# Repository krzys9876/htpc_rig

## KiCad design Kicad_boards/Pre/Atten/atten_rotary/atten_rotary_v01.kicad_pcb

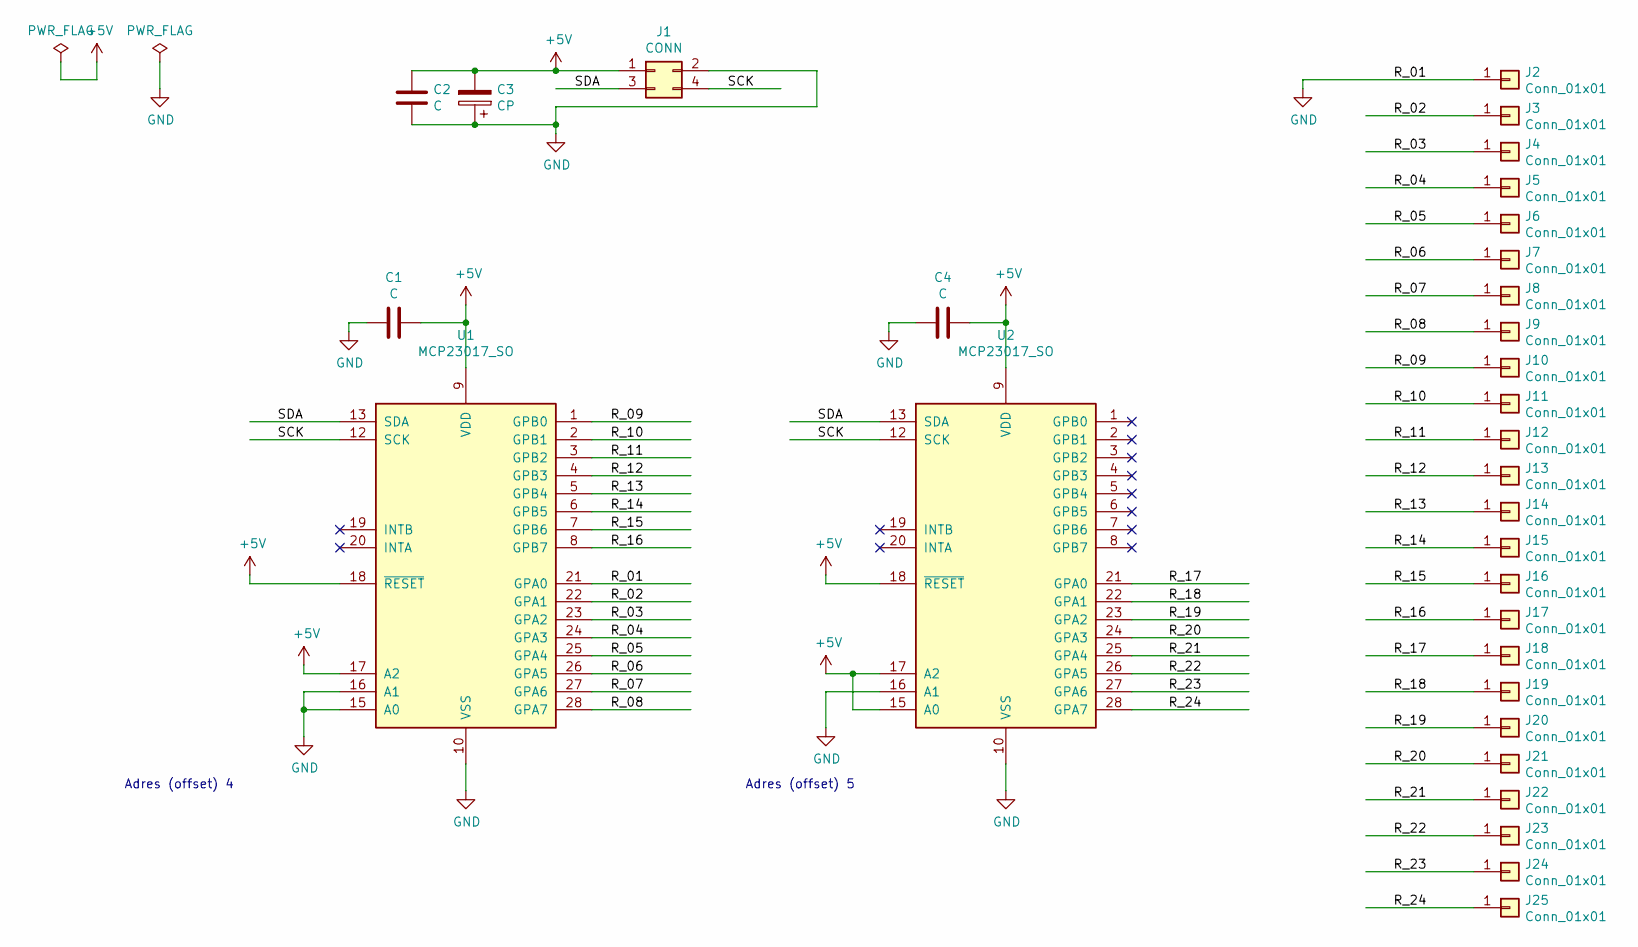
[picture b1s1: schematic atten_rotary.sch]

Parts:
C1, C2, C4: C; C_1206_3216Metric
C3: CP; C_1812_4532Metric
J1: CONN; PinHeader_2x02_P2.54mm_Vertical
J2, J3, J4, J5, J6, J7, J8, J9, J10, J11, J12, J13, J14, J15, J16, J17, J18, J19, J20, J21, J22, J23, J24, J25: Conn_01x01; PinHeader_1x01_P2.54mm_Vertical
U1, U2: MCP23017_SO; SOIC-28W_7.5x17.9mm_P1.27mm

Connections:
+5V: C1.2, C2.1, C3.2, C4.2, J1.1, U1.9 (VDD), U1.17 (A2), U1.18 (~RESET~), U2.9 (VDD), U2.15 (A0), U2.17 (A2), U2.18 (~RESET~)
/R_02: J3.1, U1.22 (GPA1)
/R_03: J4.1, U1.23 (GPA2)
/R_04: J5.1, U1.24 (GPA3)
/R_05: J6.1, U1.25 (GPA4)
/R_06: J7.1, U1.26 (GPA5)
/R_07: J8.1, U1.27 (GPA6)
/R_08: J9.1, U1.28 (GPA7)
/R_09: J10.1, U1.1 (GPB0)
/R_10: J11.1, U1.2 (GPB1)
/R_11: J12.1, U1.3 (GPB2)
/R_12: J13.1, U1.4 (GPB3)
/R_13: J14.1, U1.5 (GPB4)
/R_14: J15.1, U1.6 (GPB5)
/R_15: J16.1, U1.7 (GPB6)
/R_16: J17.1, U1.8 (GPB7)
/R_17: J18.1, U2.21 (GPA0)
/R_18: J19.1, U2.22 (GPA1)
/R_19: J20.1, U2.23 (GPA2)
/R_20: J21.1, U2.24 (GPA3)
/R_21: J22.1, U2.25 (GPA4)
/R_22: J23.1, U2.26 (GPA5)
/R_23: J24.1, U2.27 (GPA6)
/R_24: J25.1, U2.28 (GPA7)
/SCK: J1.4, U1.12 (SCK), U2.12 (SCK)
/SDA: J1.3, U1.13 (SDA), U2.13 (SDA)
GND: C1.1, C2.2, C3.1, C4.1, J1.2, J2.1, U1.10 (VSS), U1.15 (A0), U1.16 (A1), U1.21 (GPA0), U2.10 (VSS), U2.16 (A1)

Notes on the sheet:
Adres (offset) 5
Adres (offset) 4

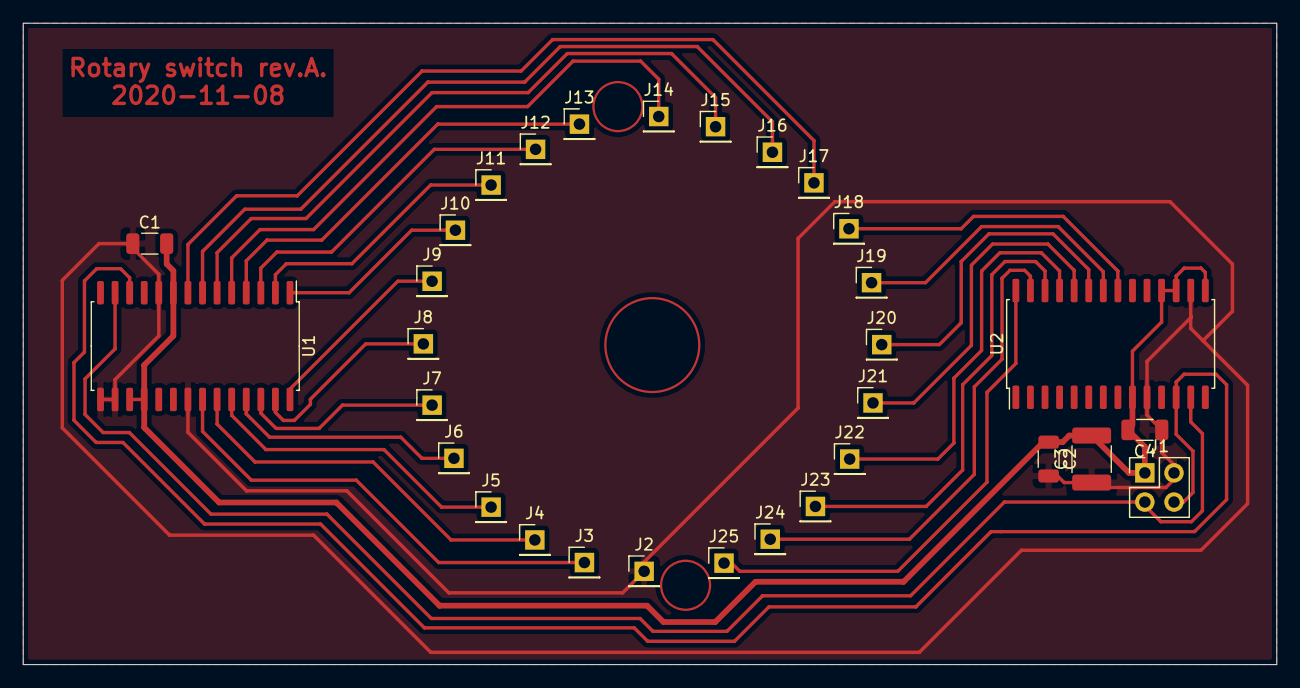
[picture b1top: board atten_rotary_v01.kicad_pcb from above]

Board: 2 copper layers, 109.2 x 55.9 mm, 31 parts (0 on the bottom side), 27 nets.

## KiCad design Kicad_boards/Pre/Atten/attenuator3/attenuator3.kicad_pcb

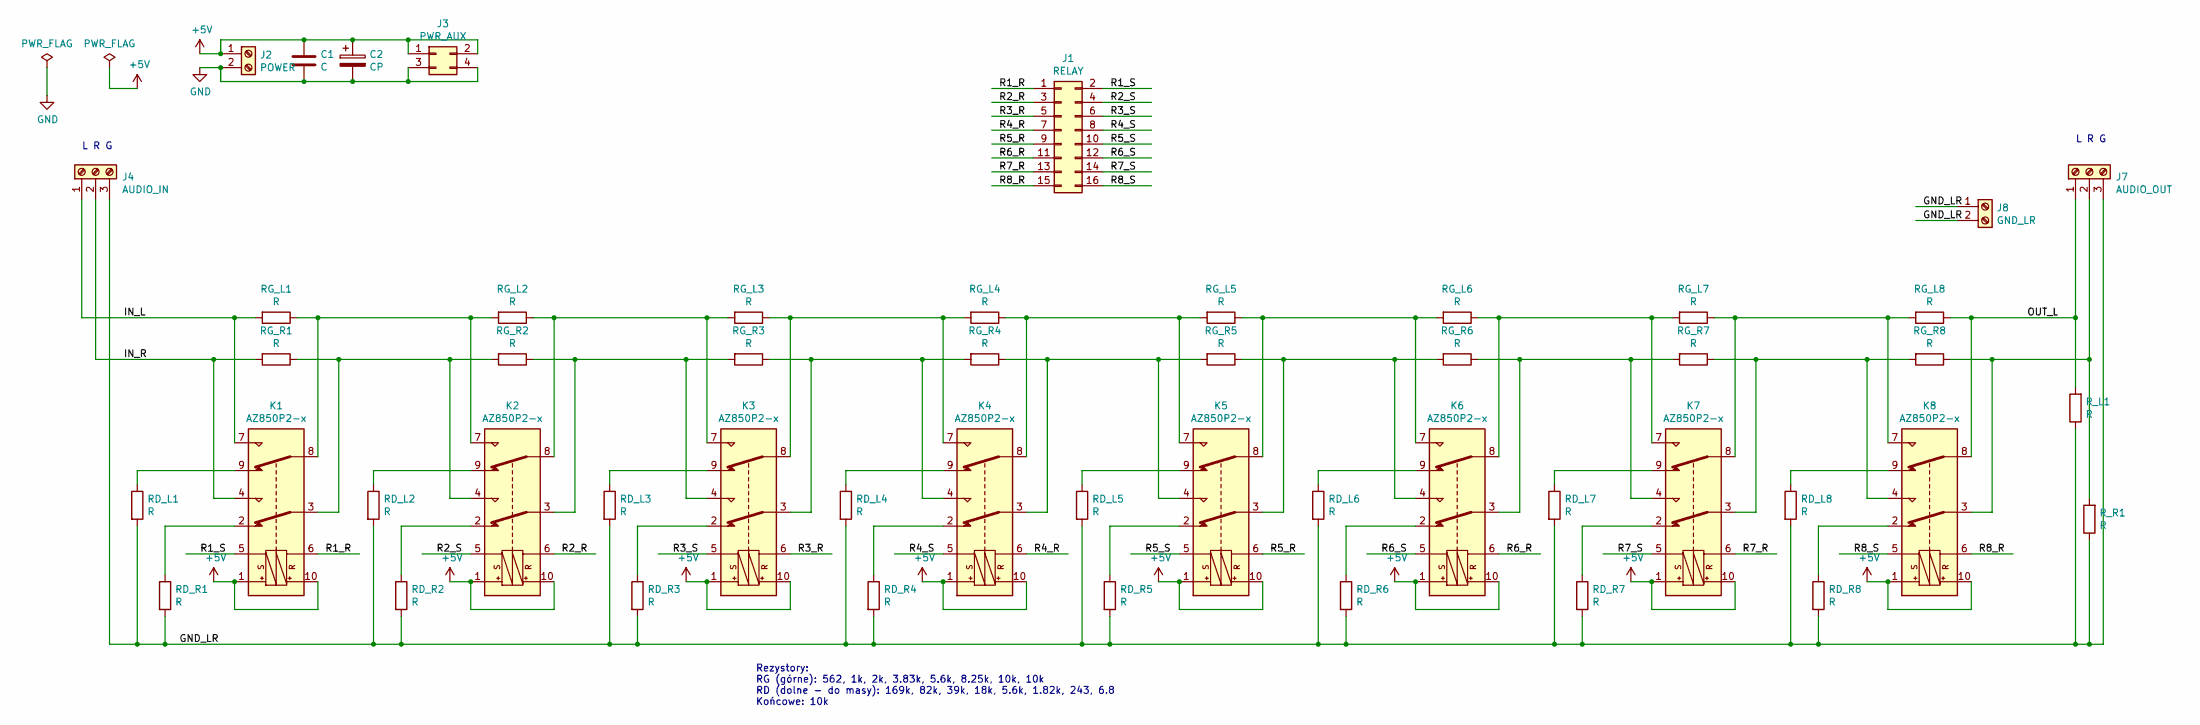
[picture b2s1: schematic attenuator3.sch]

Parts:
C1: C; C_1206_3216Metric
C2: CP; C_1210_3225Metric
J1: RELAY; PinHeader_2x08_P2.54mm_Vertical_SMD
J2: POWER; TerminalBlock_RND_205-00012_1x02_P5.00mm_Horizontal
J3: PWR_AUX; PinHeader_2x02_P2.54mm_Vertical
J4: AUDIO_IN; TerminalBlock_RND_205-00013_1x03_P5.00mm_Horizontal
J7: AUDIO_OUT; TerminalBlock_RND_205-00013_1x03_P5.00mm_Horizontal
J8: GND_LR; TerminalBlock_RND_205-00012_1x02_P5.00mm_Horizontal
K1, K2, K3, K4, K5, K6, K7, K8: AZ850P2-x; Relay_DPDT_FRT5
RD_L1, RD_L2, RD_L3, RD_L4, RD_L5, RD_L6, RD_L7, RD_L8: R; R_Axial_DIN0207_L6.3mm_D2.5mm_P10.16mm_Horizontal
RD_R1, RD_R2, RD_R3, RD_R4, RD_R5, RD_R6, RD_R7, RD_R8: R; R_Axial_DIN0207_L6.3mm_D2.5mm_P10.16mm_Horizontal
RG_L1, RG_L2, RG_L3, RG_L4, RG_L5, RG_L6, RG_L7, RG_L8: R; R_Axial_DIN0207_L6.3mm_D2.5mm_P10.16mm_Horizontal
RG_R1, RG_R2, RG_R3, RG_R4, RG_R5, RG_R6, RG_R7, RG_R8: R; R_Axial_DIN0207_L6.3mm_D2.5mm_P10.16mm_Horizontal
R_L1: R; R_Axial_DIN0207_L6.3mm_D2.5mm_P10.16mm_Horizontal
R_R1: R; R_Axial_DIN0207_L6.3mm_D2.5mm_P10.16mm_Horizontal

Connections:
+5V: C1.1, C2.1, J2.1, J3.1, J3.2, K1.1, K1.10, K2.1, K2.10, K3.1, K3.10, K4.1, K4.10, K5.1, K5.10, K6.1, K6.10, K7.1, K7.10, K8.1, K8.10
/GND_LR: J4.3, J7.3, J8.1, J8.2, RD_L1.2, RD_L2.2, RD_L3.2, RD_L4.2, RD_L5.2, RD_L6.2, RD_L7.2, RD_L8.2, RD_R1.2, RD_R2.2, RD_R3.2, RD_R4.2, RD_R5.2, RD_R6.2, RD_R7.2, RD_R8.2, R_L1.1, R_R1.1
/IN_L: J4.1, K1.7, RG_L1.2
/IN_R: J4.2, K1.4, RG_R1.2
/OUT_L: J7.1, K8.8, RG_L8.1, R_L1.2
/R1_R: J1.1, K1.6
/R1_S: J1.2, K1.5
/R2_R: J1.3, K2.6
/R2_S: J1.4, K2.5
/R3_R: J1.5, K3.6
/R3_S: J1.6, K3.5
/R4_R: J1.7, K4.6
/R4_S: J1.8, K4.5
/R5_R: J1.9, K5.6
/R5_S: J1.10, K5.5
/R6_R: J1.11, K6.6
/R6_S: J1.12, K6.5
/R7_R: J1.13, K7.6
/R7_S: J1.14, K7.5
/R8_R: J1.15, K8.6
/R8_S: J1.16, K8.5
GND: C1.2, C2.2, J2.2, J3.3, J3.4
unnamed: J7.2, K8.3, RG_R8.1, R_R1.2
unnamed: K1.2, RD_R1.1
unnamed: K1.3, K2.4, RG_R1.1, RG_R2.2
unnamed: K1.8, K2.7, RG_L1.1, RG_L2.2
unnamed: K1.9, RD_L1.1
unnamed: K2.2, RD_R2.1
unnamed: K2.3, K3.4, RG_R2.1, RG_R3.2
unnamed: K2.8, K3.7, RG_L2.1, RG_L3.2
unnamed: K2.9, RD_L2.1
unnamed: K3.2, RD_R3.1
unnamed: K3.3, K4.4, RG_R3.1, RG_R4.2
unnamed: K3.8, K4.7, RG_L3.1, RG_L4.2
unnamed: K3.9, RD_L3.1
unnamed: K4.2, RD_R4.1
unnamed: K4.3, K5.4, RG_R4.1, RG_R5.2
unnamed: K4.8, K5.7, RG_L4.1, RG_L5.2
unnamed: K4.9, RD_L4.1
unnamed: K5.2, RD_R5.1
unnamed: K5.3, K6.4, RG_R5.1, RG_R6.2
unnamed: K5.8, K6.7, RG_L5.1, RG_L6.2
unnamed: K5.9, RD_L5.1
unnamed: K6.2, RD_R6.1
unnamed: K6.3, K7.4, RG_R6.1, RG_R7.2
unnamed: K6.8, K7.7, RG_L6.1, RG_L7.2
unnamed: K6.9, RD_L6.1
unnamed: K7.2, RD_R7.1
unnamed: K7.3, K8.4, RG_R7.1, RG_R8.2
unnamed: K7.8, K8.7, RG_L7.1, RG_L8.2
unnamed: K7.9, RD_L7.1
unnamed: K8.2, RD_R8.1
unnamed: K8.9, RD_L8.1

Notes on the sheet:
Rezystory: RG (górne): 562, 1k, 2k, 3.83k, 5.6k, 8.25k, 10k, 10k RD (dolne - do masy): 169k, 82k, 39k, 18k, 5.6k, 1.82k, 243, 6.8 Końcowe: 10k
L R G

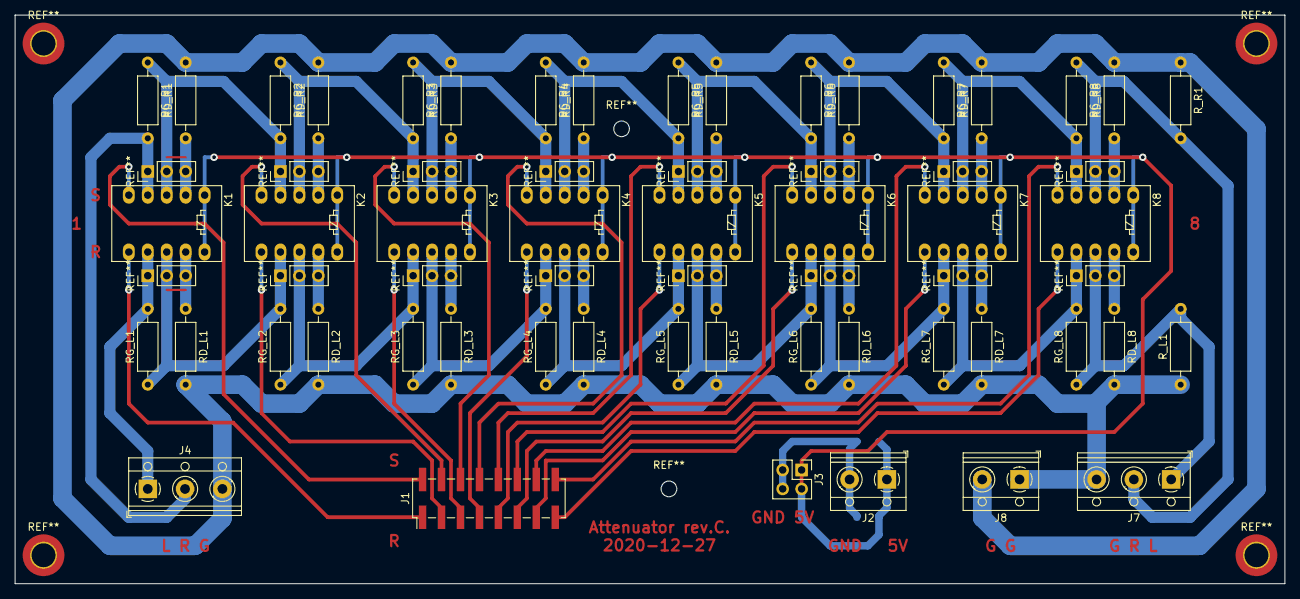
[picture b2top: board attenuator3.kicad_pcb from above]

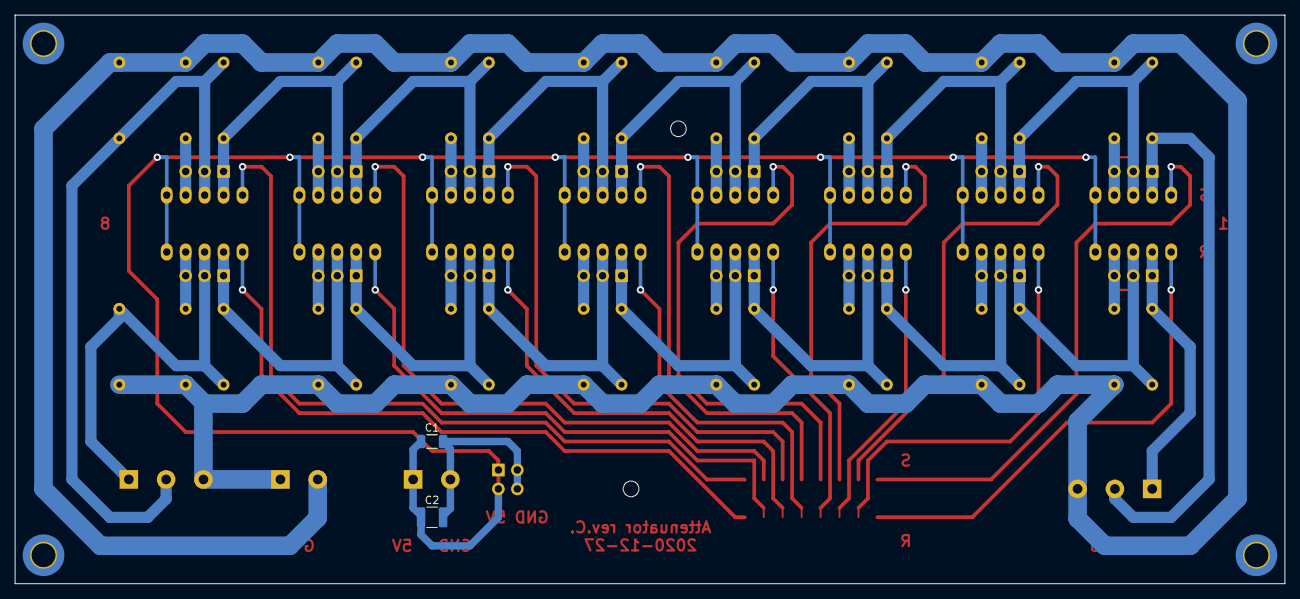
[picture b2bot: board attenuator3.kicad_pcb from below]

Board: 2 copper layers, 170.2 x 76.2 mm, 50 parts (2 on the bottom side), 53 nets.

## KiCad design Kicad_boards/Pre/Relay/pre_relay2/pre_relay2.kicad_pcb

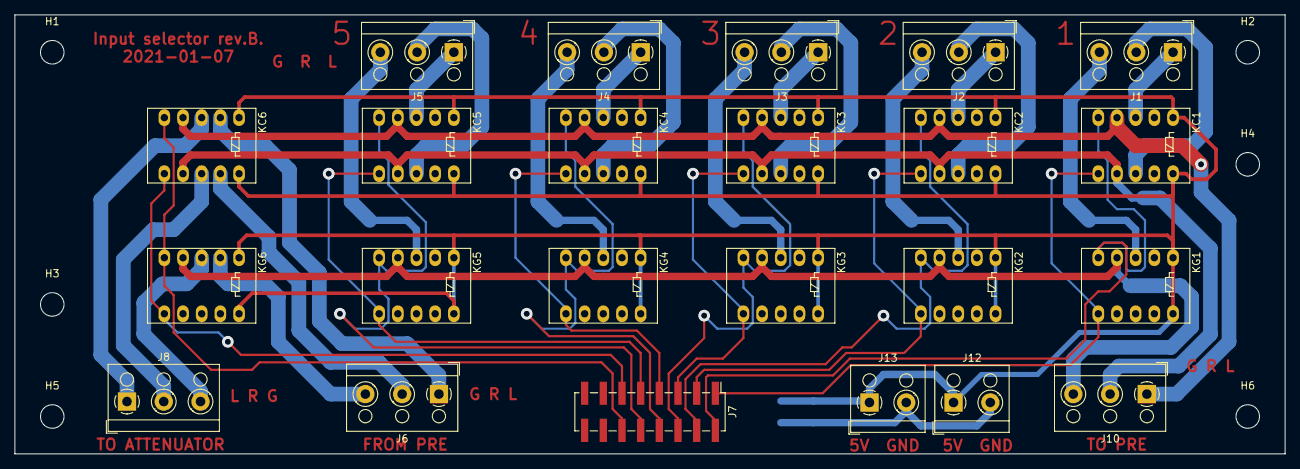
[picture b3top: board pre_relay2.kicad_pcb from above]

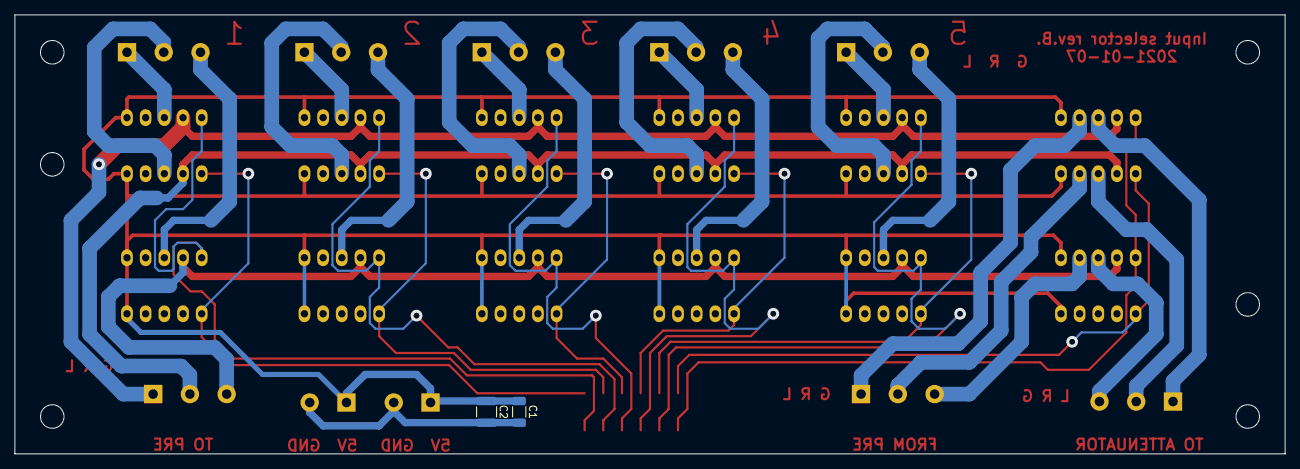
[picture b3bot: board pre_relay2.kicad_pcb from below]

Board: 2 copper layers, 172.7 x 59.7 mm, 31 parts (2 on the bottom side), 38 nets.

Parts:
C1: 100n; C_1206_3216Metric
C2: 10u; C_1210_3225Metric
H1, H2, H3, H4, H5, H6: MountingHole; MountingHole_3.2mm_M3
J1: INPUT1; TerminalBlock_RND_205-00002_1x03_P5.00mm_Horizontal
J2: INPUT2; TerminalBlock_RND_205-00002_1x03_P5.00mm_Horizontal
J3: INPUT3; TerminalBlock_RND_205-00002_1x03_P5.00mm_Horizontal
J4: INPUT4; TerminalBlock_RND_205-00002_1x03_P5.00mm_Horizontal
J5: INPUT5; TerminalBlock_RND_205-00002_1x03_P5.00mm_Horizontal
J6: OUTPUT_PRE; TerminalBlock_RND_205-00002_1x03_P5.00mm_Horizontal
J7: CONTROL; PinHeader_2x08_P2.54mm_Vertical_SMD
J8: OUTPUT; TerminalBlock_RND_205-00002_1x03_P5.00mm_Horizontal
J10: INPUT; TerminalBlock_RND_205-00002_1x03_P5.00mm_Horizontal
J12: POWER; TerminalBlock_RND_205-00001_1x02_P5.00mm_Horizontal
J13: POWER2; TerminalBlock_RND_205-00001_1x02_P5.00mm_Horizontal
KC1, KC2, KC3, KC4, KC5, KC6: AZ850P2-x; Relay_DPDT_FRT5
KG1, KG2, KG3, KG4, KG5, KG6: AZ850P2-x; Relay_DPDT_FRT5

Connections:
+5V: C1.1, C2.1, J12.1, J13.1, KC1.1, KC1.10, KC2.1, KC2.10, KC3.1, KC3.10, KC4.1, KC4.10, KC5.1, KC5.10, KC6.1, KC6.10, KG1.1, KG1.10, KG2.1, KG2.10, KG3.1, KG3.10, KG4.1, KG4.10, KG5.1, KG5.10, KG6.1, KG6.10
/R1_R: J7.1, KC1.6, KG1.6
/R1_S: J7.2, KC1.5, KG1.5
/R2_R: J7.3, KC2.6, KG2.6
/R2_S: J7.4, KC2.5, KG2.5
/R3_R: J7.5, KC3.6, KG3.6
/R3_S: J7.6, KC3.5, KG3.5
/R4_R: J7.7, KC4.6, KG4.6
/R4_S: J7.8, KC4.5, KG4.5
/R5_R: J7.9, KC5.6, KG5.6
/R5_S: J7.10, KC5.5, KG5.5
/R6_R: J7.11, KC6.6, KG6.6
/R6_S: J7.12, KC6.5, KG6.5
GND: C1.2, C2.2, J12.2, J13.2
unnamed: J1.1, KC1.3
unnamed: J1.2, KC1.8
unnamed: J1.3, KG1.3
unnamed: J2.1, KC2.3
unnamed: J2.2, KC2.8
unnamed: J2.3, KG2.3
unnamed: J3.1, KC3.3
unnamed: J3.2, KC3.8
unnamed: J3.3, KG3.3
unnamed: J4.1, KC4.3
unnamed: J4.2, KC4.8
unnamed: J4.3, KG4.3
unnamed: J5.1, KC5.3
unnamed: J5.2, KC5.8
unnamed: J5.3, KG5.3
unnamed: J6.1, KC6.2
unnamed: J6.2, KC6.9
unnamed: J6.3, KG6.2
unnamed: J8.1, KC6.3
unnamed: J8.2, KC6.8
unnamed: J8.3, KG6.3
unnamed: J10.1, KC1.4, KC2.4, KC3.4, KC4.4, KC5.4, KC6.4
unnamed: J10.2, KC1.7, KC2.7, KC3.7, KC4.7, KC5.7, KC6.7
unnamed: J10.3, KG1.4, KG2.4, KG3.4, KG4.4, KG5.4, KG6.4
